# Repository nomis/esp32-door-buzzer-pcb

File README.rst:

ESP32 Door Buzzer
=================

Overview
--------

Schematic to connect an ESP32-S3 to a door buzzer and door lock.

Purpose
-------

Use an ESP32-S3 to release the door lock and monitor when the door buzzer is
pressed.

The 12V AC from the buzzer is converted to DC and regulated to 5V for use with
the optocoupler.

The normally open relay releases the door lock by connecting 0V AC to complete
the unlocking circuit.

Usage
-----

This is a KiCad project. The PCB only exists to plan the breadboard layout to
minimise the number of wires.

* `Software for the ESP32-S3 <https://github.com/nomis/esp32-door-buzzer>`_

Schematic
----------

Header J3 is aligned to match the K1 relay on a breadboard.

Header J4 is for future use to allow the ESP32-S3 to connect/disconnect the
phone buzzer.

.. image:: render/esp32-door-buzzer-sch.svg
   :alt: Schematic

Components
----------

+---------------------+----------+--------------------------------------------------------------+
| Refs                | Quantity | Name                                                         |
+=====================+==========+==============================================================+
| C1                  |     1    | 100µF Capacitor, Through Hole                                |
+---------------------+----------+--------------------------------------------------------------+
| C2                  |     1    | 0.1µF Capacitor, Through Hole                                |
+---------------------+----------+--------------------------------------------------------------+
| D1                  |     1    | Multicomp MP606G Bridge Rectifier, Through Hole              |
+---------------------+----------+--------------------------------------------------------------+
| D2                  |     1    | 1N4004 Diode, Through Hole                                   |
+---------------------+----------+--------------------------------------------------------------+
| J1, J2              |     2    | 1x20 Pin Socket, Through Hole (2.54mm)                       |
+---------------------+----------+--------------------------------------------------------------+
| J3                  |     1    | 1x06 Pin Header, Through Hole (2.54mm)                       |
+---------------------+----------+--------------------------------------------------------------+
| J4                  |     2    | 1x02 Pin Header, Through Hole (2.54mm)                       |
+---------------------+----------+--------------------------------------------------------------+
| K1                  |     1    | HUI KE HK4100F 5V Relay, Through Hole                        |
+---------------------+----------+--------------------------------------------------------------+
| Q1                  |     1    | ON Semiconductor BS170 N-Channel MOSFET, TO-92-3             |
+---------------------+----------+--------------------------------------------------------------+
| R1                  |     1    | 390Ω Resistor, Through Hole                                  |
+---------------------+----------+--------------------------------------------------------------+
| R2                  |     1    | 10kΩ Resistor, Through Hole                                  |
+---------------------+----------+--------------------------------------------------------------+
| R3                  |     1    | 1kΩ Resistor, Through Hole                                   |
+---------------------+----------+--------------------------------------------------------------+
| U1                  |     1    | ON Semiconductor FOD817 Optocoupler, DIP-4                   |
+---------------------+----------+--------------------------------------------------------------+
| U2                  |     1    | STMicroelectronics L78L12 Voltage Regulator, TO-92-3         |
+---------------------+----------+--------------------------------------------------------------+

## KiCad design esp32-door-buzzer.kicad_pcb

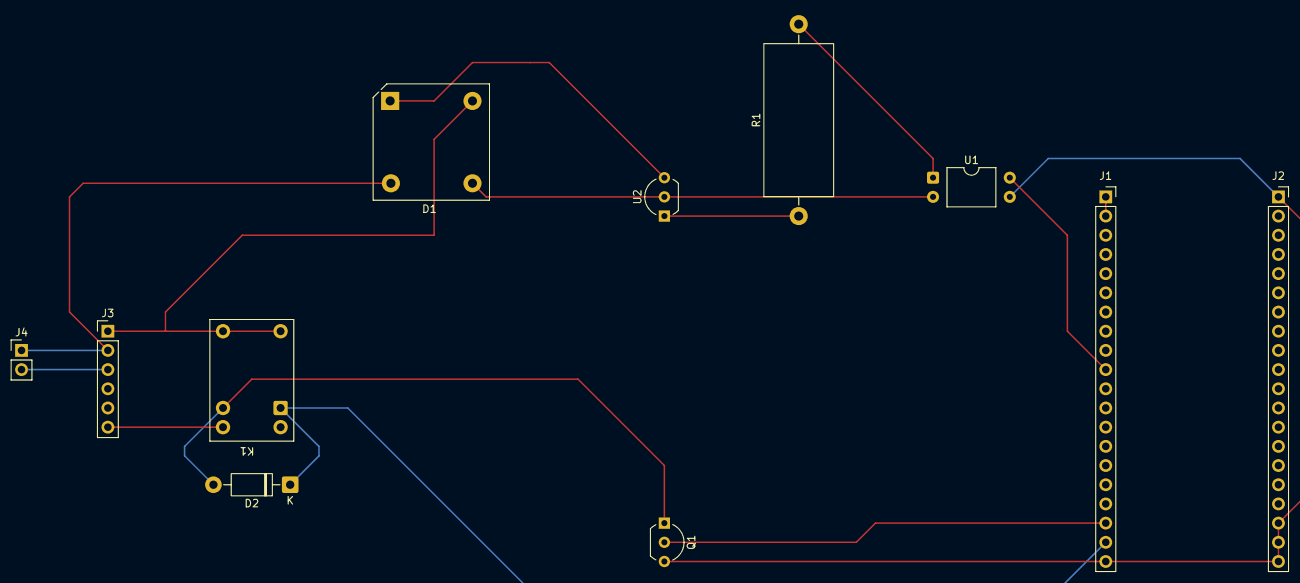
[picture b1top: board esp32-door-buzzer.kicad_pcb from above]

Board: 2 copper layers, 11 parts (0 on the bottom side), 14 nets.

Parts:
D1: D_Bridge_+A-A; Diode_Bridge_15.1x15.1x6.3mm_P10.9mm
D2: 1N4004; D_DO-41_SOD81_P10.16mm_Horizontal
J1, J2: ESP32-S3; PinSocket_1x20_P2.54mm_Vertical
J3: Conn_01x06_Pin; PinHeader_1x06_P2.54mm_Vertical
J4: Conn_01x02_Pin; PinHeader_1x02_P2.54mm_Vertical
K1: HK4100F-DC5V-SHG; Relay_SPDT_CUI_SR5
Q1: NMOS; TO-92_Inline_Wide
R1: 390Ω; R_Axial_DIN0922_L20.0mm_D9.0mm_P25.40mm_Horizontal
U1: Optocoupler_DC_PhotoNPN_AKEC; DIP-4_W10.16mm
U2: L78L12_TO92; TO-92_Inline_Wide

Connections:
+3.3V: J1.1, J1.2
+5V: D2.1 (K), J1.19, K1.2
/0V: D1.4, J3.1, K1.5
/BUZZER: J3.3, J4.2
/GPIO12: J1.18, Q1.2 (G)
/GPIO17: J1.10, U1.4
/OPEN: J3.6, K1.10
/RING: D1.2, J3.2, J4.1
GND: J1.20, J2.1, J2.18, J2.19, J2.20, Q1.3 (S), U1.3
unnamed: D1.1 (+), U2.3 (VI)
unnamed: D1.3 (-), U1.2, U2.2 (GND)
unnamed: D2.2 (A), K1.9, Q1.1 (D)
unnamed: R1.2, U1.1
unnamed: R1.1, U2.1 (VO)

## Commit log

2026-04-08 Change transistor to a mosfet
2026-04-11 Add resistors to manage the mosfet properly
2026-06-18 Add README and schematic rendering
2026-06-18 Add relay diode to the component list
2026-06-19 Add more details
2026-06-27 Link to software
